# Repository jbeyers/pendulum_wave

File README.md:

# A perpetual pendulum wave machine

## What is it?

A pendulum wave is formed by a row of pendulums, each with a slightly different period. When started at the same time, they swing in a row, but quickly turn into a sinewavey snake shape, go through a whole set of interesting patterns and then end up in a straight row again.

The only ones I've seen are started and tuned manually.

## But perpetual?

Using steel bearing balls with magnets for the pendulums, and giving them a bit of a kick every now and again with a wire solenoid coil, the pendulums can be made to swing continuously. However, they would go out of tune after a few cycles.

The length of the pendulums are adjustable, so I can get them pretty close.

Getting the pendulums to vary their period is the tricky bit. This is slightly difficult to explain, but since the pendulums are built with fishing line, I can add a secondary pivot point below the first one, which will only kick in once the swing is larger than a certain angle. This causes the overall period to shorten if the angle increases.

Each coil has a sensing circuit to detect the pendulum swinging overhead. The coil is slightly offset to one side so that it can determine the direction of the swing from the slight difference in sensing time between the left and right swings.

Each coil is pulsed under PID control, so they sync up no matter what the initial positions are.

## License

This repository contains various files. In general, licensing is CC-BY-SA-4.0 for the designs and MIT for the software. Let me know if you need clarification.

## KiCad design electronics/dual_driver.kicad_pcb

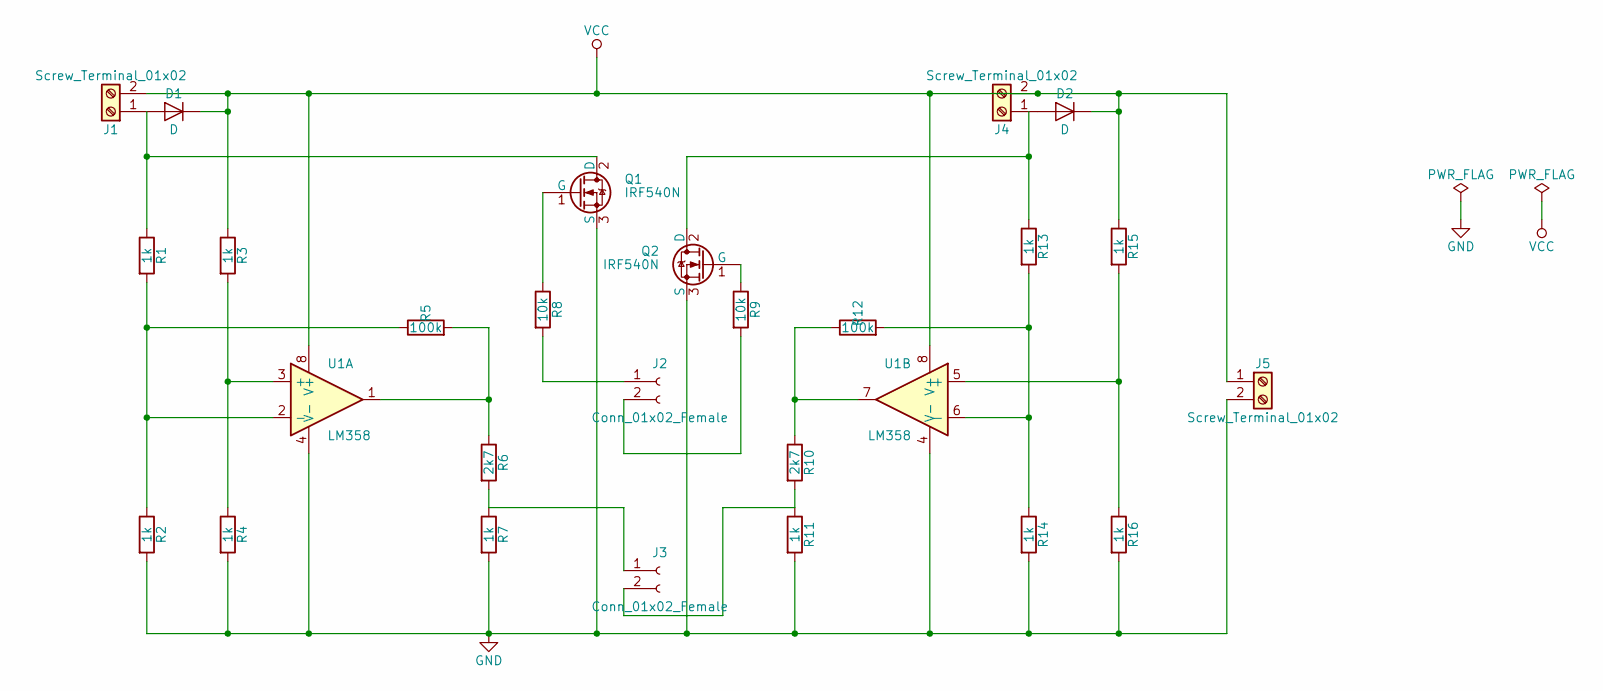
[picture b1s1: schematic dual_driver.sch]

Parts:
D1, D2: D; D_DO-41_SOD81_P2.54mm_Vertical_AnodeUp
J1, J4: Screw_Terminal_01x02; TerminalBlock_Phoenix_MPT-2.54mm_2pol
J2, J3: Conn_01x02_Female; Socket_Strip_Straight_1x02_Pitch2.54mm
J5: Screw_Terminal_01x02; TerminalBlock_bornier-2_P5.08mm
Q1, Q2: IRF540N; TO-220-3_Vertical
R1, R2, R3, R4, R7, R11, R13, R14, R15, R16: 1k; R_Axial_DIN0516_L15.5mm_D5.0mm_P20.32mm_Horizontal
R5, R12: 100k; R_Axial_DIN0516_L15.5mm_D5.0mm_P20.32mm_Horizontal
R6, R10: 2k7; R_Axial_DIN0516_L15.5mm_D5.0mm_P20.32mm_Horizontal
R8, R9: 10k; R_Axial_DIN0516_L15.5mm_D5.0mm_P20.32mm_Horizontal
U1: LM358; DIP-8_W7.62mm

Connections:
GND: J5.2, Q1.3 (S), Q2.3 (S), R2.2, R4.2, R7.2, R11.2, R14.2, R16.2, U1.4 (V-)
unnamed: D1.2 (A), J1.1, Q1.2 (D), R1.1
unnamed: D2.2 (A), J4.1
unnamed: J2.1, R8.2
unnamed: J2.2, R9.2
unnamed: J3.1, R6.2, R7.1
unnamed: J3.2, R10.2, R11.1
unnamed: Q1.1 (G), R8.1
unnamed: Q2.1 (G), R9.1
unnamed: Q2.2 (D), R13.1
unnamed: R1.2, R2.1, R5.1, U1.2 (-)
unnamed: R3.2, R4.1, U1.3 (+)
unnamed: R5.2, R6.1, U1.1
unnamed: R10.1, R12.1, U1.7
unnamed: R12.2, R13.2, R14.1, U1.6 (-)
unnamed: R15.2, R16.1, U1.5 (+)
VCC: D1.1 (K), D2.1 (K), J1.2, J4.2, J5.1, R3.1, R15.1, U1.8 (V+)

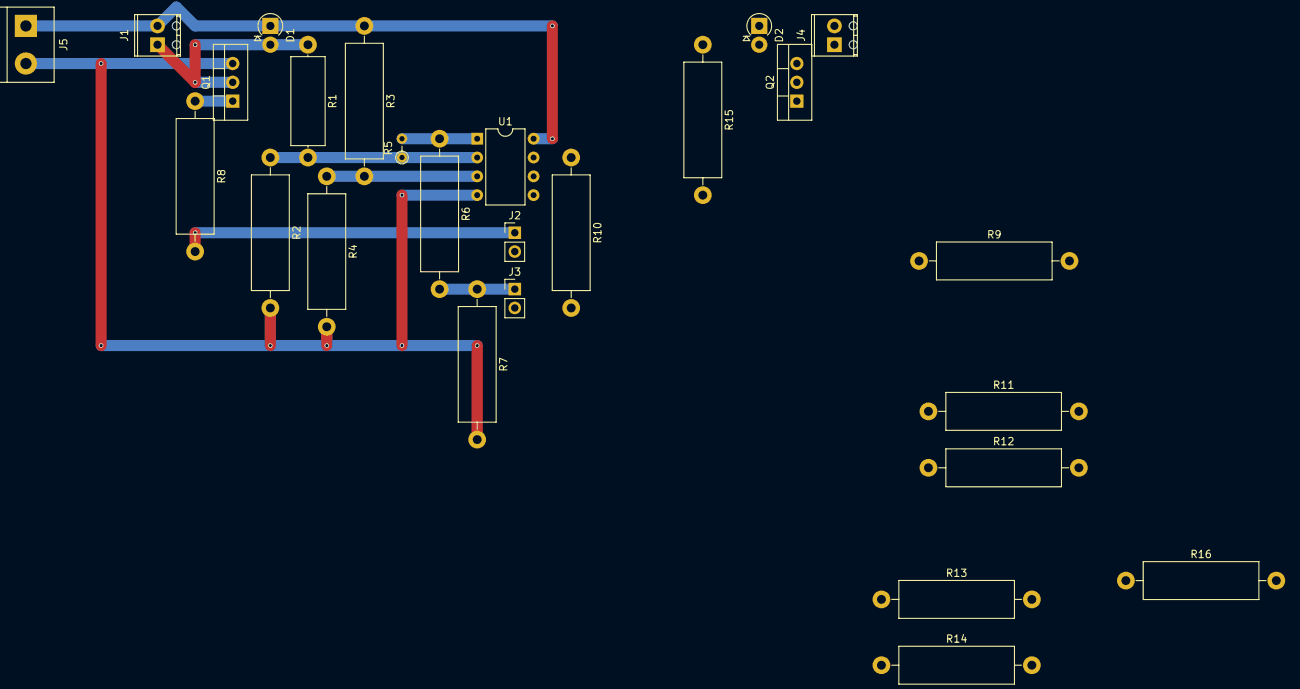
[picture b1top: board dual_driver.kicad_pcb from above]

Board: 2 copper layers, 26 parts (0 on the bottom side), 17 nets.

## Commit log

2016-07-23 Plan outline
2016-07-23 Added thoughts on license
2016-07-23 Holder for the pendulum balls added
2016-07-25 Add square tubing cut list spreadsheet
2016-07-25 Add alternative physical control mechanism.
2016-07-26 Test program for pendulum period
2016-07-27 Calculate pendulum timings
2016-07-27 Working pendulum pulse generator
2016-08-07 Remove stl files
2016-08-07 Added extra cross items
2016-08-07 Some parts added
2016-08-07 Ignore generated files
2016-08-07 Simple washers
2016-08-08 Thicker washers
2016-08-09 Basic adjuster
2016-08-09 Pulse a bit longer
2016-08-16 Parts all created individually
2016-08-16 Combine fitting parts into assembly
2016-08-22 Tweak parts
2016-08-23 Basic tuner program
2016-08-23 Line length calc for pendulums
2016-08-25 Newer attempt at setting timings
2017-10-03 Add notes after ordering magnet wire
2017-10-03 Fix bullet points
2017-11-13 Testing code with coil pickups
2017-11-22 New cleaner wave with coil triggering
2017-11-22 Add pcb design files
2017-11-22 Ignore kicad pcb and autogenerated files
2017-11-25 Tweak and add viewing
2017-12-01 Semi-working, but switching too slowly
2017-12-02 Go through all pendulums
2017-12-02 Switch randomly and proportional control
2017-12-02 Proportional lockouts brings better imbalance detection
2017-12-02 Clamp proportional and remove trigger levels
2017-12-02 Cleanup and fix logic
2017-12-03 Get average swing times and predict next trigger
2017-12-03 Remove unused trigger average
2017-12-03 Working with spaced pulsing
2017-12-03 Faster imbalance correction, better diagnostics. It Works!
2017-12-03 Tweak some parameters
2017-12-08 Lots of comments, little bit of code. Prep for PID
2017-12-09 PID control
2018-02-04 Nice descriptions for thingiverse customizer
2018-02-04 Update readme to indicate the project is done.
2018-02-04 Remove old and testing code
2018-02-04 Adjust cut list with new dimensions
2018-02-04 Design files updated
2018-03-22 Added trimpots to schematic
2018-04-28 More solid ball holder with cutout for magnet
2018-05-03 Larger magnet
2018-05-04 Thicker holder
2019-04-25 Minimum angle set for ball holders
2021-12-16 New wave
2023-09-14 Fix wording
